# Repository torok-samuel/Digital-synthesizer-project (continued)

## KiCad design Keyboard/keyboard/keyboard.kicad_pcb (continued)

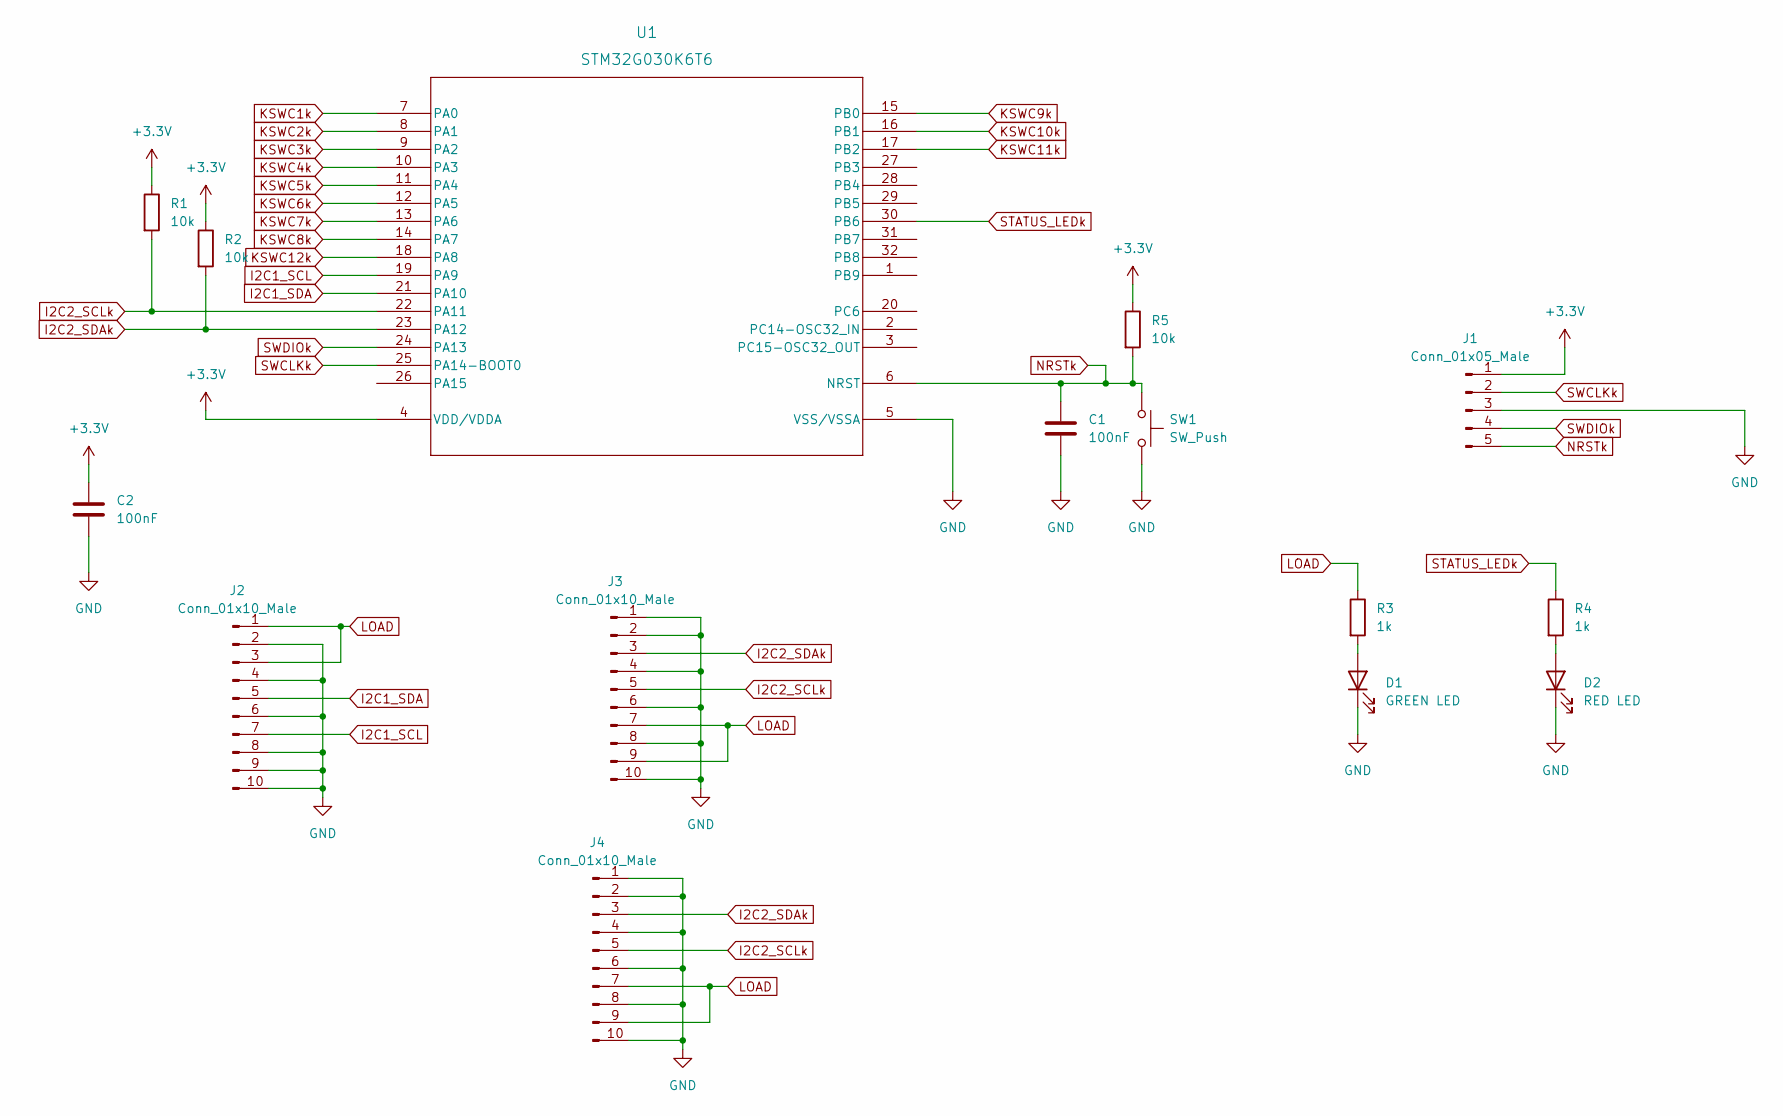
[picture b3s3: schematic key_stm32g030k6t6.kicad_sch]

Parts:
C1, C2: 100nF; C_0805_2012Metric_Pad1.18x1.45mm_HandSolder
D1: GREEN LED; LED_0805_2012Metric_Pad1.15x1.40mm_HandSolder
D2: RED LED; LED_0805_2012Metric_Pad1.15x1.40mm_HandSolder
J1: Conn_01x05_Male; PinSocket_1x05_P2.54mm_Vertical
J2, J3, J4: Conn_01x10_Male; IDC-Header_2x05_P2.54mm_Horizontal
R1, R2, R5: 10k; R_0805_2012Metric_Pad1.20x1.40mm_HandSolder
R3, R4: 1k; R_0805_2012Metric_Pad1.20x1.40mm_HandSolder
SW1: SW_Push; ROCPU Switches TP10721645
U1: STM32G030K6T6; LQFP-32

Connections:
+3V3: C2.1, J1.1, R1.1, R2.1, R5.1, U1.4 (VDD/VDDA); also elsewhere on the board
GND: C1.2, C2.2, D1.1 (K), D2.1 (K), J1.3, J2.2, J2.4, J2.6, J2.8, J2.9, J2.10, J3.1, J3.2, J3.4, J3.6, J3.8, J3.10, J4.1, J4.2, J4.4, J4.6, J4.8, J4.10, SW1.2, U1.5 (VSS/VSSA); also elsewhere on the board
I2C1_SCL: J2.7, U1.19 (PA9)
I2C1_SDA: J2.5, U1.21 (PA10)
I2C2_SCLk: J3.5, J4.5, R1.2, U1.22 (PA11)
I2C2_SDAk: J3.3, J4.3, R2.2, U1.23 (PA12)
KSWC1k: U1.7 (PA0); also elsewhere on the board
KSWC2k: U1.8 (PA1); also elsewhere on the board
KSWC3k: U1.9 (PA2); also elsewhere on the board
KSWC4k: U1.10 (PA3); also elsewhere on the board
KSWC5k: U1.11 (PA4); also elsewhere on the board
KSWC6k: U1.12 (PA5); also elsewhere on the board
KSWC7k: U1.13 (PA6); also elsewhere on the board
KSWC8k: U1.14 (PA7); also elsewhere on the board
KSWC9k: U1.15 (PB0); also elsewhere on the board
KSWC10k: U1.16 (PB1); also elsewhere on the board
KSWC11k: U1.17 (PB2); also elsewhere on the board
KSWC12k: U1.18 (PA8); also elsewhere on the board
LOAD: J2.1, J2.3, J3.7, J3.9, J4.7, J4.9, R3.1; also elsewhere on the board
NRSTk: C1.1, J1.5, R5.2, SW1.1, U1.6 (NRST)
unnamed: D1.2 (A), R3.2
unnamed: D2.2 (A), R4.2
STATUS_LEDk: R4.1, U1.30 (PB6)
SWCLKk: J1.2, U1.25 (PA14-BOOT0)
SWDIOk: J1.4, U1.24 (PA13)

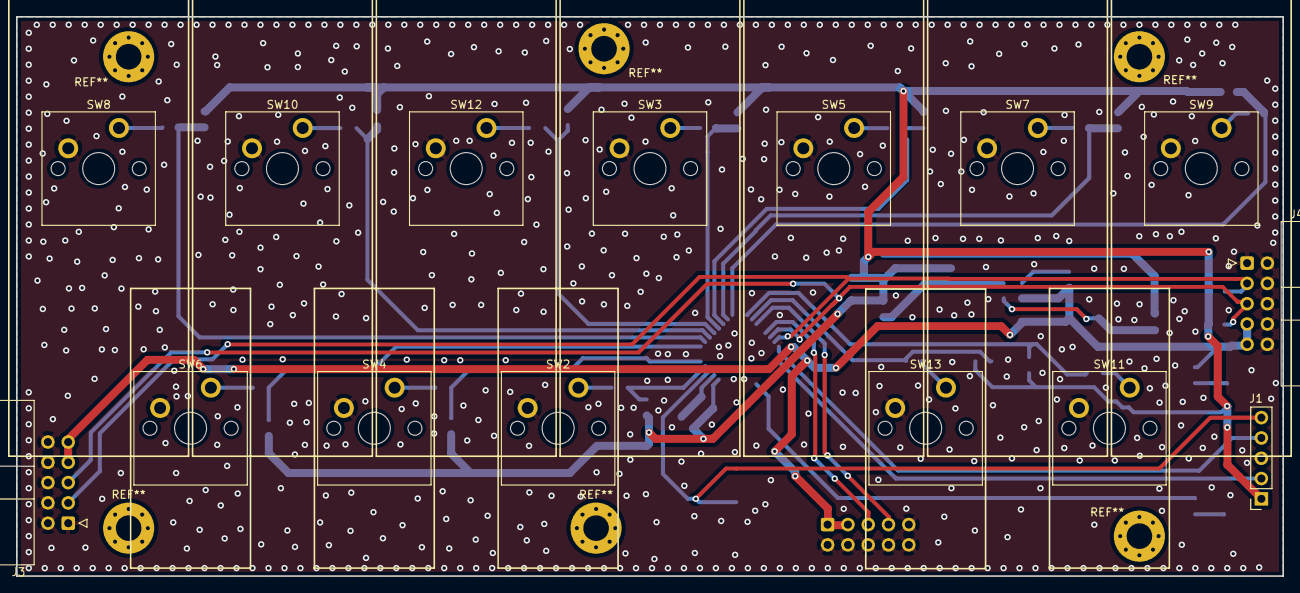
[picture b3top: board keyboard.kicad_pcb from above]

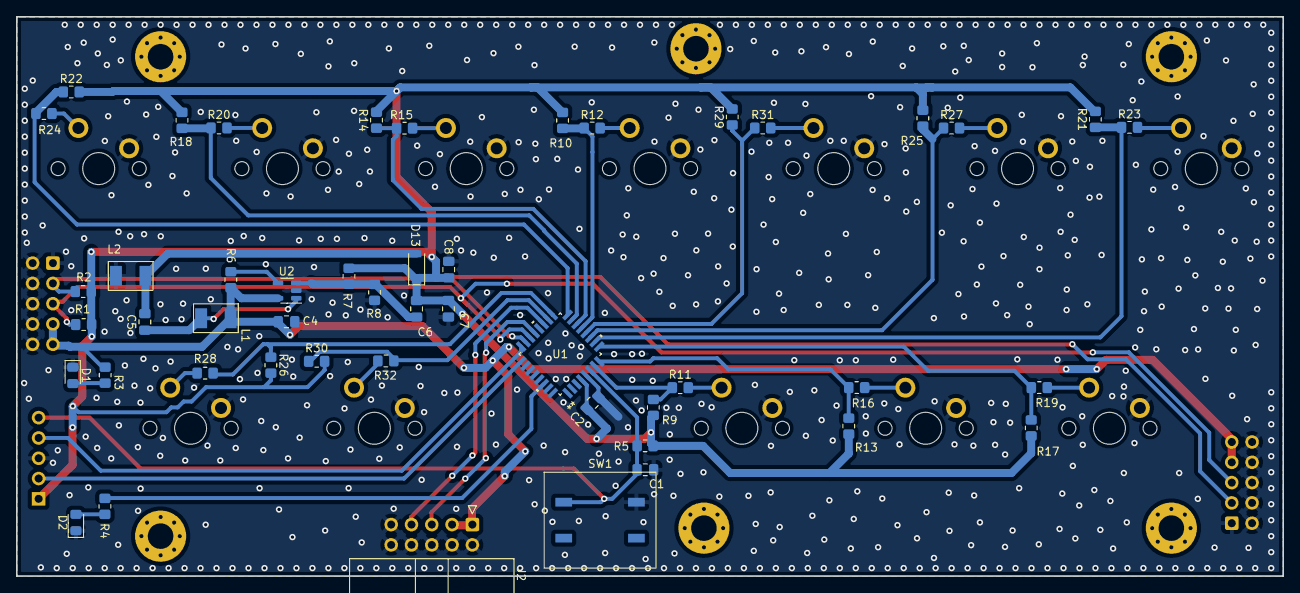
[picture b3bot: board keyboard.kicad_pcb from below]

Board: 2 copper layers, 158.5 x 70.0 mm, 63 parts (48 on the bottom side), 41 nets.

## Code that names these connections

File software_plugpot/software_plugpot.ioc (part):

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Mcu.Name=STM32G030K(6-8)Tx
Mcu.Package=LQFP32
Mcu.UserName=STM32G030K6Tx
PA0.Mode=IN0
PA0.Signal=ADC1_IN0
PA1.Mode=IN1
PA1.Signal=ADC1_IN1
PA10.Mode=I2C
PA10.Signal=I2C1_SDA
PA12\ [PA10].Signal=ADC1_IN16
PA13.Mode=Serial_Wire
PA13.Signal=SYS_SWDIO
PA14-BOOT0.Mode=Serial_Wire
PA14-BOOT0.Signal=SYS_SWCLK
PA2.Mode=IN2
PA2.Signal=ADC1_IN2
PA3.Mode=IN3
PA3.Signal=ADC1_IN3
PA4.Mode=IN4
PA4.Signal=ADC1_IN4
PA5.Mode=IN5
PA5.Signal=ADC1_IN5
PA6.Mode=IN6
PA6.Signal=ADC1_IN6
PA7.Mode=IN7
PA7.Signal=ADC1_IN7
PA8.GPIOParameters=GPIO_Label
PA8.GPIO_Label=SW1p
PA8.Signal=GPIO_Input
PA9.Mode=I2C
PA9.Signal=I2C1_SCL
PB0.Mode=IN8
PB0.Signal=ADC1_IN8
PB1.Mode=IN9
PB1.Signal=ADC1_IN9
PB2.Mode=IN10
PB2.Signal=ADC1_IN10
PB3.GPIOParameters=GPIO_Label
PB3.GPIO_Label=SW3p
PB3.Signal=GPIO_Input
PB4.GPIOParameters=GPIO_Label
PB4.GPIO_Label=SW4p
PB4.Signal=GPIO_Input
PB5.GPIOParameters=GPIO_Label
PB5.GPIO_Label=SW5p
PB5.Signal=GPIO_Input
PB6.GPIOParameters=GPIO_Label
PB6.GPIO_Label=SW6p
PB6.Signal=GPIO_Input
PB7.GPIOParameters=GPIO_Label
PB7.GPIO_Label=SW7p
PB7.Signal=GPIO_Input
PB8.GPIOParameters=GPIO_Label
PB8.GPIO_Label=SW8p
PB8.Signal=GPIO_Input
PB9.GPIOParameters=GPIO_Label
PB9.GPIO_Label=STATUS_LED
PB9.Signal=GPIO_Output
PC6.GPIOParameters=GPIO_Label
PC6.GPIO_Label=SW2p
PC6.Signal=GPIO_Input
RCC.HSE_VALUE=8000000
RCC.SYSCLKFreq_VALUE=16000000
board=custom

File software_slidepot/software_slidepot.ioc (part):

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Mcu.Name=STM32G030K(6-8)Tx
Mcu.Package=LQFP32
Mcu.UserName=STM32G030K6Tx
PA0.Mode=IN0
PA0.Signal=ADC1_IN0
PA1.Mode=IN1
PA1.Signal=ADC1_IN1
PA10.Mode=I2C
PA10.Signal=I2C1_SDA
PA11\ [PA9].GPIOParameters=GPIO_Label
PA11\ [PA9].GPIO_Label=R3
PA11\ [PA9].Signal=GPIO_Input
PA12\ [PA10].GPIOParameters=GPIO_Label
PA12\ [PA10].GPIO_Label=R2
PA12\ [PA10].Signal=GPIO_Input
PA13.Mode=Serial_Wire
PA13.Signal=SYS_SWDIO
PA14-BOOT0.Mode=Serial_Wire
PA14-BOOT0.Signal=SYS_SWCLK
PA15.GPIOParameters=GPIO_Label
PA15.GPIO_Label=R1
PA15.Signal=GPIO_Input
PA2.Mode=IN2
PA2.Signal=ADC1_IN2
PA3.Mode=IN3
PA3.Signal=ADC1_IN3
PA4.Mode=IN4
PA4.Signal=ADC1_IN4
PA5.Mode=IN5
PA5.Signal=ADC1_IN5
PA6.Mode=IN6
PA6.Signal=ADC1_IN6
PA7.Mode=IN7
PA7.Signal=ADC1_IN7
PA8.GPIOParameters=GPIO_Label
PA8.GPIO_Label=R5
PA8.Signal=GPIO_Input
PA9.Mode=I2C
PA9.Signal=I2C1_SCL
PB3.GPIOParameters=GPIO_Label
PB3.GPIO_Label=C1
PB3.Signal=GPIO_Output
PB4.GPIOParameters=GPIO_Label
PB4.GPIO_Label=C2
PB4.Signal=GPIO_Output
PB5.GPIOParameters=GPIO_Label
PB5.GPIO_Label=C3
PB5.Signal=GPIO_Output
PB7.GPIOParameters=GPIO_Label
PB7.GPIO_Label=LEDS
PB7.Mode=PWM Generation1 CH1N
PB7.Signal=TIM17_CH1N
PB8.GPIOParameters=GPIO_Label
PB8.GPIO_Label=C4
PB8.Signal=GPIO_Output
PB9.GPIOParameters=GPIO_Label
PB9.GPIO_Label=C5
PB9.Signal=GPIO_Output
PC15-OSC32_OUT\ (PC15).GPIOParameters=GPIO_Label
PC15-OSC32_OUT\ (PC15).GPIO_Label=STATUS_LED
PC15-OSC32_OUT\ (PC15).Signal=GPIO_Output
PC6.GPIOParameters=GPIO_Label
PC6.GPIO_Label=R4
PC6.Signal=GPIO_Input
RCC.HSE_VALUE=8000000
RCC.SYSCLKFreq_VALUE=16000000
board=custom

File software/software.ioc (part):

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Mcu.Name=STM32F446R(C-E)Tx
Mcu.Package=LQFP64
Mcu.UserName=STM32F446RETx
PA10.Mode=Asynchronous
PA10.Signal=USART1_RX
PA11.Mode=Device_Only
PA11.Signal=USB_OTG_FS_DM
PA12.Mode=Device_Only
PA12.Signal=USB_OTG_FS_DP
PA13.Mode=JTAG_5_pins
PA13.Signal=SYS_JTMS-SWDIO
PA14.Mode=JTAG_5_pins
PA14.Signal=SYS_JTCK-SWCLK
PA15.Mode=JTAG_5_pins
PA15.Signal=SYS_JTDI
PA4.Mode=Half_Duplex_Master
PA4.Signal=I2S1_WS
PA5.Mode=Half_Duplex_Master
PA5.Signal=I2S1_CK
PA7.Mode=Half_Duplex_Master
PA7.Signal=I2S1_SD
PA9.Mode=Asynchronous
PA9.Signal=USART1_TX
PB10.Mode=Simplex_Bidirectional_Master
PB10.Signal=SPI2_SCK
PB12.Signal=GPIO_Output
PB3.Mode=JTAG_5_pins
PB3.Signal=SYS_JTDO-SWO
PB4.Mode=JTAG_5_pins
PB4.Signal=SYS_JTRST
PB6.Mode=I2C
PB6.Signal=I2C1_SCL
PB7.Mode=I2C
PB7.Signal=I2C1_SDA
PC1.Mode=Simplex_Bidirectional_Master
PC1.Signal=SPI2_MOSI
PC10.Mode=Asynchronous
PC10.Signal=USART3_TX
PC4.Mode=Master_Clock_Activated
PC4.Signal=I2S1_MCK
PC5.Mode=Asynchronous
PC5.Signal=USART3_RX
PH0-OSC_IN.Mode=HSE-External-Oscillator
PH0-OSC_IN.Signal=RCC_OSC_IN
PH1-OSC_OUT.Mode=HSE-External-Oscillator
PH1-OSC_OUT.Signal=RCC_OSC_OUT
RCC.HSE_VALUE=8000000
board=custom

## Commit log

2023-04-24 forgot other 2 projects
2023-04-25 main func schematics fixed
2023-04-26 fixing keyboard and pot project schematics
2023-04-28 main_func pcb done
2023-04-30 Pot.but_pcb in progress
2023-05-01 Pot.butt_pcb done
2023-05-02 PCB designs done v1
2023-05-08 pcb design fixing
2023-05-08 pcb mounting hole change
2023-05-13 gerber files generated
2023-09-14 Software added
2023-10-19 DDS synth added
2023-10-30 Freecad files added
2023-10-30 CLEANUP DONE Bitbang reset failed for 250ms error => slave reset
2023-10-30 Forgot WhiteKey3
2023-11-02 BLIST B-Slave func added (not completed)
2023-11-07 freecad files fixed
2023-11-16 matlab files added, blit sawtooth programming started
2023-11-30 blit implementation in stm32
